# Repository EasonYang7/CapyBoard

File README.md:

# CapyBoard

Capyboard is a custom designed 80% TKL with custom knobs & OLED screen to fuel the exciting daily workload!

Inspired from the cute Capybara, the keyboard is a cozy comfort to all students studying for exams, and locking in for academics :)

## Features:
- Top & Bottom 3D Modelled Case
- 1x 128x64 OLED Display
- 2x Rotary Knob
- 79x RGB LEDs
- 79x Keys
- KMK Support

## BOM:
- 79x Cherry MX Switches
- 79x SK6812 Mini LEDs
- 79x 1N4148 Diodes
- 1x 128x64 OLED Screen
- 2x 4.7k 0603 Resistors
- 2x EC11E Rotary Encoders
- 1x Seeed Studio Xiao
- 1x Raspberry Pi Pico
- 1x Keycap Set

## Microcontroller
This keyboard supports two microcontroller options:
- Seeed Studio Xiao RP2040 (Main Usage)
- Raspberry Pi Pico (Alternative Usage if Needed)

Both firmware files will be used for seperate input purposes

## Flashing Firmware:

### Step 1 - Install MicroPython
1. Hold BOOTSEL Button on XIAO, and plug in USB-C
2. Download MicroPython .uf2 from https://micropython.org/download/SEEED_XIAO_RP2040/
3. Drag and Drop .uf2 file into RPI-RP2 Drive

### Step 2 - Install KMK
1. Download KMK from https://github.com/KMKfw/kmk_firmware
2. Copy the kmk folder to my XIAO

**Step 3 - Flash Keyboard Firmware**
1. Copy XIAO_code.py to your XIAO and rename it main.py

## Assembly
- Solder components using the schematic as reference
- Install switches onto PCB
- 3D Print the Case
- Use M2 Screws to Assemble the Chassis
- Flash Firmware onto the Keyboard!

## Usage
- Plug USB-C Cable to the Seeed Xiao Studio RP2040
- Keys are Mapped, and can be Modified using KMK!

## Pictures
Schematics:

PCB:

3D Model:

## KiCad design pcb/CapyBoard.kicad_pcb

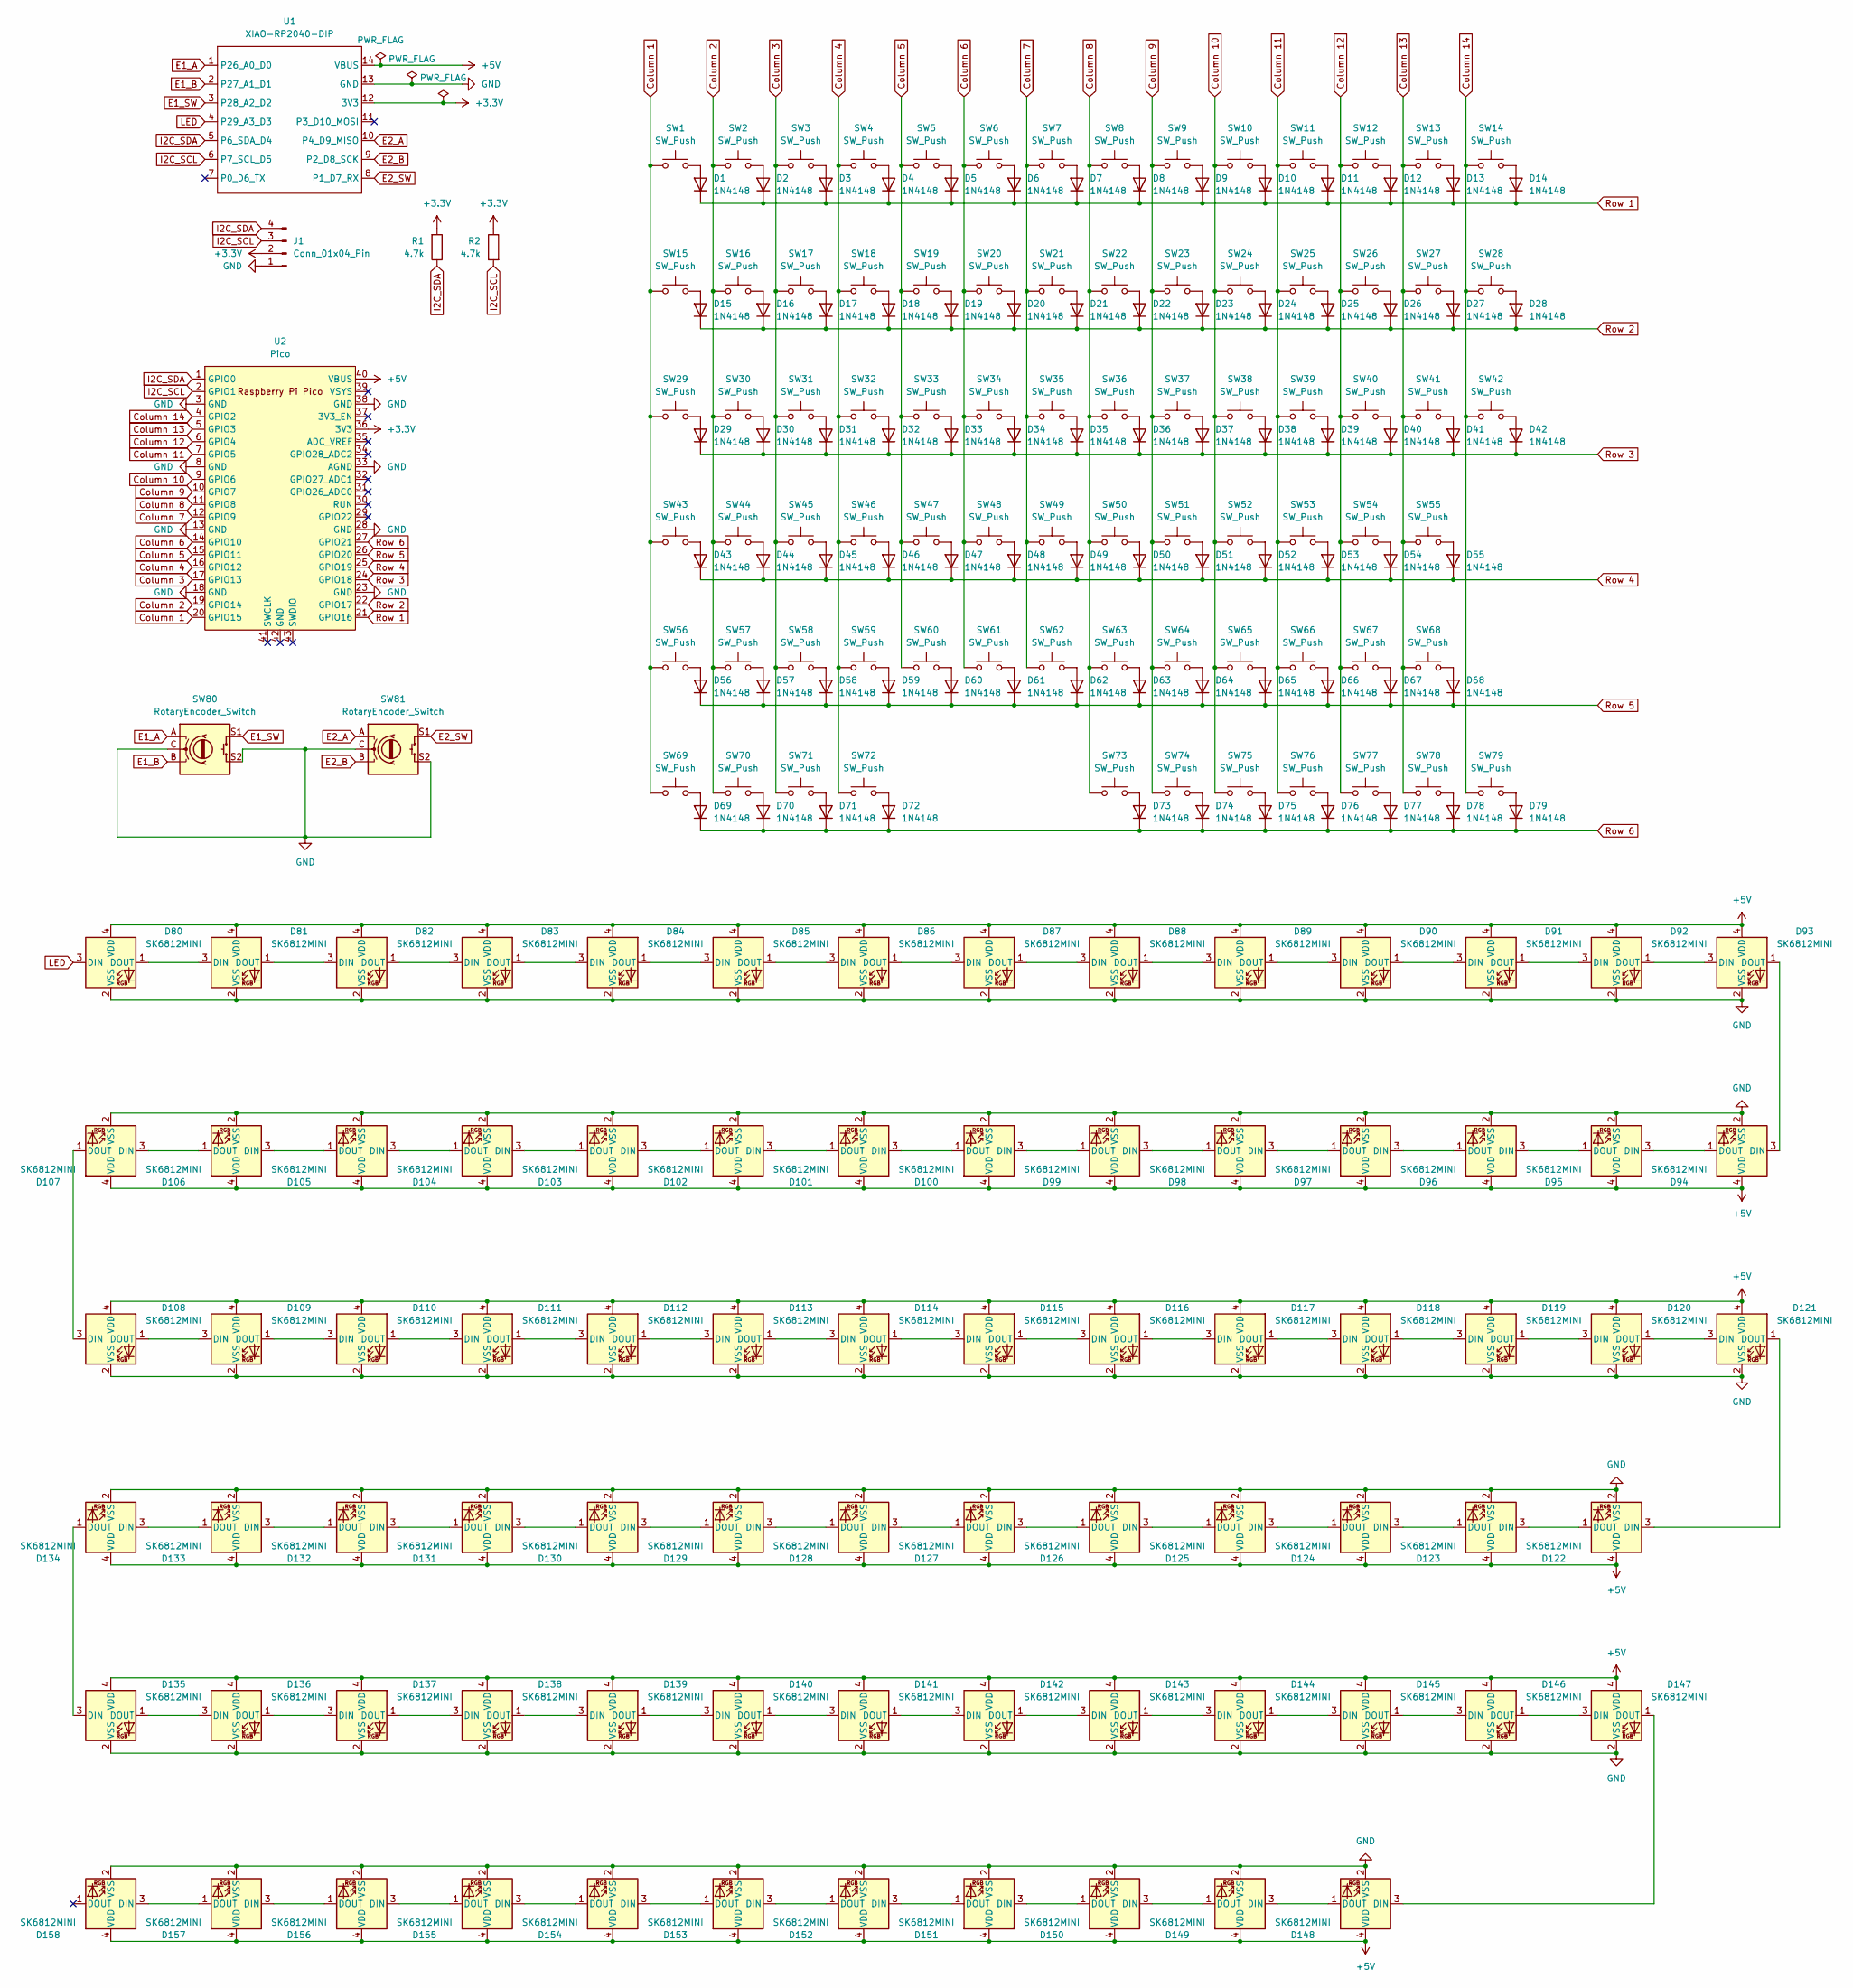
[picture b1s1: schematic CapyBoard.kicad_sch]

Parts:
D1, D2, D3, D4, D5, D6, D7, D8, D9, D10, D11, D12, D13, D14, D15, D16, D17, D18, D19, D20, D21, D22, D23, D24, D25, D26, D27, D28, D29, D30, D31, D32, D33, D34, D35, D36, D37, D38, D39, D40, D41, D42, D43, D44, D45, D46, D47, D48, D49, D50, D51, D52, D53, D54, D55, D56, D57, D58, D59, D60, D61, D62, D63, D64, D65, D66, D67, D68, D69, D70, D71, D72, D73, D74, D75, D76, D77, D78, D79: 1N4148; D_DO-35_SOD27_P7.62mm_Horizontal
D80, D81, D82, D83, D84, D85, D86, D87, D88, D89, D90, D91, D92, D93, D94, D95, D96, D97, D98, D99, D100, D101, D102, D103, D104, D105, D106, D107, D108, D109, D110, D111, D112, D113, D114, D115, D116, D117, D118, D119, D120, D121, D122, D123, D124, D125, D126, D127, D128, D129, D130, D131, D132, D133, D134, D135, D136, D137, D138, D139, D140, D141, D142, D143, D144, D145, D146, D147, D148, D149, D150, D151, D152, D153, D154, D155, D156, D157, D158: SK6812MINI; LED_SK6812MINI_PLCC4_3.5x3.5mm_P1.75mm
J1: Conn_01x04_Pin; 128x64OLED
R1, R2: 4.7k; R_0603_1608Metric_Pad0.98x0.95mm_HandSolder
SW1, SW2, SW3, SW4, SW5, SW6, SW7, SW8, SW9, SW10, SW11, SW12, SW13, SW14, SW15, SW16, SW17, SW18, SW19, SW20, SW21, SW22, SW23, SW24, SW25, SW26, SW27, SW30, SW31, SW32, SW33, SW34, SW35, SW36, SW37, SW38, SW39, SW40, SW41, SW44, SW45, SW46, SW47, SW48, SW49, SW50, SW51, SW52, SW53, SW54, SW57, SW58, SW59, SW60, SW61, SW62, SW63, SW64, SW65, SW66, SW68, SW77, SW78, SW79: SW_Push; SW_Cherry_MX_1.00u_PCB
SW28: SW_Push; SW_Cherry_MX_2.00u_PCB
SW29, SW42: SW_Push; SW_Cherry_MX_1.50u_PCB
SW43: SW_Push; SW_Cherry_MX_1.75u_PCB
SW55, SW56: SW_Push; SW_Cherry_MX_2.25u_PCB
SW67: SW_Push; SW_Cherry_MX_2.75u_PCB
SW69, SW70, SW71, SW73, SW74, SW75, SW76: SW_Push; SW_Cherry_MX_1.25u_PCB
SW72: SW_Push; SW_Cherry_MX_6.25u_PCB
SW80, SW81: RotaryEncoder_Switch; RotaryEncoder_Alps_EC11E-Switch_Vertical_H20mm_CircularMoun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
U1: XIAO-RP2040-DIP
U2: Pico; RPi_Pico_SMD_TH

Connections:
+3.3V: J1.2, R1.2, R2.1, U1.12 (3V3), U2.36 (3V3)
+5V: D80.4 (VDD), D81.4 (VDD), D82.4 (VDD), D83.4 (VDD), D84.4 (VDD), D85.4 (VDD), D86.4 (VDD), D87.4 (VDD), D88.4 (VDD), D89.4 (VDD), D90.4 (VDD), D91.4 (VDD), D92.4 (VDD), D93.4 (VDD), D94.4 (VDD), D95.4 (VDD), D96.4 (VDD), D97.4 (VDD), D98.4 (VDD), D99.4 (VDD), D100.4 (VDD), D101.4 (VDD), D102.4 (VDD), D103.4 (VDD), D104.4 (VDD), D105.4 (VDD), D106.4 (VDD), D107.4 (VDD), D108.4 (VDD), D109.4 (VDD), D110.4 (VDD), D111.4 (VDD), D112.4 (VDD), D113.4 (VDD), D114.4 (VDD), D115.4 (VDD), D116.4 (VDD), D117.4 (VDD), D118.4 (VDD), D119.4 (VDD), D120.4 (VDD), D121.4 (VDD), D122.4 (VDD), D123.4 (VDD), D124.4 (VDD), D125.4 (VDD), D126.4 (VDD), D127.4 (VDD), D128.4 (VDD), D129.4 (VDD), D130.4 (VDD), D131.4 (VDD), D132.4 (VDD), D133.4 (VDD), D134.4 (VDD), D135.4 (VDD), D136.4 (VDD), D137.4 (VDD), D138.4 (VDD), D139.4 (VDD), D140.4 (VDD), D141.4 (VDD), D142.4 (VDD), D143.4 (VDD), D144.4 (VDD), D145.4 (VDD), D146.4 (VDD), D147.4 (VDD), D148.4 (VDD), D149.4 (VDD), D150.4 (VDD), D151.4 (VDD), D152.4 (VDD), D153.4 (VDD), D154.4 (VDD), D155.4 (VDD), D156.4 (VDD), D157.4 (VDD), D158.4 (VDD), U1.14 (VBUS), U2.40 (VBUS)
Column 1: SW1.1, SW15.1, SW29.1, SW43.1, SW56.1, SW69.1, U2.20 (GPIO15)
Column 2: SW2.1, SW16.1, SW30.1, SW44.1, SW57.1, SW70.1, U2.19 (GPIO14)
Column 3: SW3.1, SW17.1, SW31.1, SW45.1, SW58.1, SW71.1, U2.17 (GPIO13)
Column 4: SW4.1, SW18.1, SW32.1, SW46.1, SW59.1, SW72.1, U2.16 (GPIO12)
Column 5: SW5.1, SW19.1, SW33.1, SW47.1, SW60.1, U2.15 (GPIO11)
Column 6: SW6.1, SW20.1, SW34.1, SW48.1, SW61.1, U2.14 (GPIO10)
Column 7: SW7.1, SW21.1, SW35.1, SW49.1, SW62.1, U2.12 (GPIO9)
Column 8: SW8.1, SW22.1, SW36.1, SW50.1, SW63.1, SW73.1, U2.11 (GPIO8)
Column 9: SW9.1, SW23.1, SW37.1, SW51.1, SW64.1, SW74.1, U2.10 (GPIO7)
Column 10: SW10.1, SW24.1, SW38.1, SW52.1, SW65.1, SW75.1, U2.9 (GPIO6)
Column 11: SW11.1, SW25.1, SW39.1, SW53.1, SW66.1, SW76.1, U2.7 (GPIO5)
Column 12: SW12.1, SW26.1, SW40.1, SW54.1, SW67.1, SW77.1, U2.6 (GPIO4)
Column 13: SW13.1, SW27.1, SW41.1, SW55.1, SW68.1, SW78.1, U2.5 (GPIO3)
Column 14: SW14.1, SW28.1, SW42.1, SW79.1, U2.4 (GPIO2)
E1_A: SW80.A, U1.1 (P26_A0_D0)
E1_B: SW80.B, U1.2 (P27_A1_D1)
E1_SW: SW80.S1, U1.3 (P28_A2_D2)
E2_A: SW81.A, U1.10 (P4_D9_MISO)
E2_B: SW81.B, U1.9 (P2_D8_SCK)
E2_SW: SW81.S1, U1.8 (P1_D7_RX)
GND: D80.2 (VSS), D81.2 (VSS), D82.2 (VSS), D83.2 (VSS), D84.2 (VSS), D85.2 (VSS), D86.2 (VSS), D87.2 (VSS), D88.2 (VSS), D89.2 (VSS), D90.2 (VSS), D91.2 (VSS), D92.2 (VSS), D93.2 (VSS), D94.2 (VSS), D95.2 (VSS), D96.2 (VSS), D97.2 (VSS), D98.2 (VSS), D99.2 (VSS), D100.2 (VSS), D101.2 (VSS), D102.2 (VSS), D103.2 (VSS), D104.2 (VSS), D105.2 (VSS), D106.2 (VSS), D107.2 (VSS), D108.2 (VSS), D109.2 (VSS), D110.2 (VSS), D111.2 (VSS), D112.2 (VSS), D113.2 (VSS), D114.2 (VSS), D115.2 (VSS), D116.2 (VSS), D117.2 (VSS), D118.2 (VSS), D119.2 (VSS), D120.2 (VSS), D121.2 (VSS), D122.2 (VSS), D123.2 (VSS), D124.2 (VSS), D125.2 (VSS), D126.2 (VSS), D127.2 (VSS), D128.2 (VSS), D129.2 (VSS), D130.2 (VSS), D131.2 (VSS), D132.2 (VSS), D133.2 (VSS), D134.2 (VSS), D135.2 (VSS), D136.2 (VSS), D137.2 (VSS), D138.2 (VSS), D139.2 (VSS), D140.2 (VSS), D141.2 (VSS), D142.2 (VSS), D143.2 (VSS), D144.2 (VSS), D145.2 (VSS), D146.2 (VSS), D147.2 (VSS), D148.2 (VSS), D149.2 (VSS), D150.2 (VSS), D151.2 (VSS), D152.2 (VSS), D153.2 (VSS), D154.2 (VSS), D155.2 (VSS), D156.2 (VSS), D157.2 (VSS), D158.2 (VSS), J1.1, SW80.C, SW80.MP, SW80.S2, SW81.C, SW81.MP, SW81.S2, U1.13 (GND), U2.3 (GND), U2.8 (GND), U2.13 (GND), U2.18 (GND), U2.23 (GND), U2.28 (GND), U2.33 (AGND), U2.38 (GND)
I2C_SCL: J1.3, R2.2, U1.6 (P7_SCL_D5), U2.2 (GPIO1)
I2C_SDA: J1.4, R1.1, U1.5 (P6_SDA_D4), U2.1 (GPIO0)
LED: D80.3 (DIN), U1.4 (P29_A3_D3)
unnamed: D1.2 (A), SW1.2
unnamed: D2.2 (A), SW2.2
unnamed: D3.2 (A), SW3.2
unnamed: D4.2 (A), SW4.2
unnamed: D5.2 (A), SW5.2
unnamed: D6.2 (A), SW6.2
unnamed: D7.2 (A), SW7.2
unnamed: D8.2 (A), SW8.2
unnamed: D9.2 (A), SW9.2
unnamed: D10.2 (A), SW10.2
unnamed: D11.2 (A), SW11.2
unnamed: D12.2 (A), SW12.2
unnamed: D13.2 (A), SW13.2
unnamed: D14.2 (A), SW14.2
unnamed: D15.2 (A), SW15.2
unnamed: D16.2 (A), SW16.2
unnamed: D17.2 (A), SW17.2
unnamed: D18.2 (A), SW18.2
unnamed: D19.2 (A), SW19.2
unnamed: D20.2 (A), SW20.2
unnamed: D21.2 (A), SW21.2
unnamed: D22.2 (A), SW22.2
unnamed: D23.2 (A), SW23.2
unnamed: D24.2 (A), SW24.2
unnamed: D25.2 (A), SW25.2
unnamed: D26.2 (A), SW26.2
unnamed: D27.2 (A), SW27.2
unnamed: D28.2 (A), SW28.2
unnamed: D29.2 (A), SW29.2
unnamed: D30.2 (A), SW30.2
unnamed: D31.2 (A), SW31.2
unnamed: D32.2 (A), SW32.2
unnamed: D33.2 (A), SW33.2
unnamed: D34.2 (A), SW34.2
unnamed: D35.2 (A), SW35.2
unnamed: D36.2 (A), SW36.2
unnamed: D37.2 (A), SW37.2
unnamed: D38.2 (A), SW38.2
unnamed: D39.2 (A), SW39.2
unnamed: D40.2 (A), SW40.2
unnamed: D41.2 (A), SW41.2
unnamed: D42.2 (A), SW42.2
unnamed: D43.2 (A), SW43.2
unnamed: D44.2 (A), SW44.2
unnamed: D45.2 (A), SW45.2
unnamed: D46.2 (A), SW46.2
unnamed: D47.2 (A), SW47.2
unnamed: D48.2 (A), SW48.2
unnamed: D49.2 (A), SW49.2
unnamed: D50.2 (A), SW50.2
unnamed: D51.2 (A), SW51.2
unnamed: D52.2 (A), SW52.2
unnamed: D53.2 (A), SW53.2
unnamed: D54.2 (A), SW54.2
unnamed: D55.2 (A), SW55.2
unnamed: D56.2 (A), SW56.2
unnamed: D57.2 (A), SW57.2
unnamed: D58.2 (A), SW58.2
unnamed: D59.2 (A), SW59.2
unnamed: D60.2 (A), SW60.2
unnamed: D61.2 (A), SW61.2
unnamed: D62.2 (A), SW62.2
unnamed: D63.2 (A), SW63.2
unnamed: D64.2 (A), SW64.2
unnamed: D65.2 (A), SW65.2
unnamed: D66.2 (A), SW66.2
unnamed: D67.2 (A), SW67.2
unnamed: D68.2 (A), SW68.2
unnamed: D69.2 (A), SW69.2
unnamed: D70.2 (A), SW70.2
unnamed: D71.2 (A), SW71.2
unnamed: D72.2 (A), SW72.2
unnamed: D73.2 (A), SW73.2
unnamed: D74.2 (A), SW74.2
unnamed: D75.2 (A), SW75.2
unnamed: D76.2 (A), SW76.2
unnamed: D77.2 (A), SW77.2
unnamed: D78.2 (A), SW78.2
unnamed: D79.2 (A), SW79.2
unnamed: D80.1 (DOUT), D81.3 (DIN)
unnamed: D81.1 (DOUT), D82.3 (DIN)
unnamed: D82.1 (DOUT), D83.3 (DIN)
unnamed: D83.1 (DOUT), D84.3 (DIN)
unnamed: D84.1 (DOUT), D85.3 (DIN)
unnamed: D85.1 (DOUT), D86.3 (DIN)
unnamed: D86.1 (DOUT), D87.3 (DIN)
unnamed: D87.1 (DOUT), D88.3 (DIN)
unnamed: D88.1 (DOUT), D89.3 (DIN)
unnamed: D89.1 (DOUT), D90.3 (DIN)
unnamed: D90.1 (DOUT), D91.3 (DIN)
unnamed: D91.1 (DOUT), D92.3 (DIN)
unnamed: D92.1 (DOUT), D93.3 (DIN)
unnamed: D93.1 (DOUT), D94.3 (DIN)
unnamed: D94.1 (DOUT), D95.3 (DIN)
unnamed: D95.1 (DOUT), D96.3 (DIN)
unnamed: D96.1 (DOUT), D97.3 (DIN)
unnamed: D97.1 (DOUT), D98.3 (DIN)
unnamed: D98.1 (DOUT), D99.3 (DIN)
unnamed: D99.1 (DOUT), D100.3 (DIN)
unnamed: D100.1 (DOUT), D101.3 (DIN)
unnamed: D101.1 (DOUT), D102.3 (DIN)
unnamed: D102.1 (DOUT), D103.3 (DIN)
unnamed: D103.1 (DOUT), D104.3 (DIN)
unnamed: D104.1 (DOUT), D105.3 (DIN)
unnamed: D105.1 (DOUT), D106.3 (DIN)
unnamed: D106.1 (DOUT), D107.3 (DIN)
unnamed: D107.1 (DOUT), D108.3 (DIN)
unnamed: D108.1 (DOUT), D109.3 (DIN)
unnamed: D109.1 (DOUT), D110.3 (DIN)
unnamed: D110.1 (DOUT), D111.3 (DIN)
unnamed: D111.1 (DOUT), D112.3 (DIN)
unnamed: D112.1 (DOUT), D113.3 (DIN)
unnamed: D113.1 (DOUT), D114.3 (DIN)
unnamed: D114.1 (DOUT), D115.3 (DIN)
unnamed: D115.1 (DOUT), D116.3 (DIN)
unnamed: D116.1 (DOUT), D117.3 (DIN)
unnamed: D117.1 (DOUT), D118.3 (DIN)
unnamed: D118.1 (DOUT), D119.3 (DIN)
unnamed: D119.1 (DOUT), D120.3 (DIN)
unnamed: D120.1 (DOUT), D121.3 (DIN)
unnamed: D121.1 (DOUT), D122.3 (DIN)
unnamed: D122.1 (DOUT), D123.3 (DIN)
unnamed: D123.1 (DOUT), D124.3 (DIN)
unnamed: D124.1 (DOUT), D125.3 (DIN)
unnamed: D125.1 (DOUT), D126.3 (DIN)
unnamed: D126.1 (DOUT), D127.3 (DIN)
unnamed: D127.1 (DOUT), D128.3 (DIN)
unnamed: D128.1 (DOUT), D129.3 (DIN)
unnamed: D129.1 (DOUT), D130.3 (DIN)
unnamed: D130.1 (DOUT), D131.3 (DIN)
unnamed: D131.1 (DOUT), D132.3 (DIN)
unnamed: D132.1 (DOUT), D133.3 (DIN)
unnamed: D133.1 (DOUT), D134.3 (DIN)
unnamed: D134.1 (DOUT), D135.3 (DIN)
unnamed: D135.1 (DOUT), D136.3 (DIN)
unnamed: D136.1 (DOUT), D137.3 (DIN)
unnamed: D137.1 (DOUT), D138.3 (DIN)
unnamed: D138.1 (DOUT), D139.3 (DIN)
unnamed: D139.1 (DOUT), D140.3 (DIN)
unnamed: D140.1 (DOUT), D141.3 (DIN)
unnamed: D141.1 (DOUT), D142.3 (DIN)
unnamed: D142.1 (DOUT), D143.3 (DIN)
unnamed: D143.1 (DOUT), D144.3 (DIN)
unnamed: D144.1 (DOUT), D145.3 (DIN)
unnamed: D145.1 (DOUT), D146.3 (DIN)
unnamed: D146.1 (DOUT), D147.3 (DIN)
unnamed: D147.1 (DOUT), D148.3 (DIN)
unnamed: D148.1 (DOUT), D149.3 (DIN)
unnamed: D149.1 (DOUT), D150.3 (DIN)
unnamed: D150.1 (DOUT), D151.3 (DIN)
unnamed: D151.1 (DOUT), D152.3 (DIN)
unnamed: D152.1 (DOUT), D153.3 (DIN)
unnamed: D153.1 (DOUT), D154.3 (DIN)
unnamed: D154.1 (DOUT), D155.3 (DIN)
unnamed: D155.1 (DOUT), D156.3 (DIN)
unnamed: D156.1 (DOUT), D157.3 (DIN)
unnamed: D157.1 (DOUT), D158.3 (DIN)
Row 1: D1.1 (K), D2.1 (K), D3.1 (K), D4.1 (K), D5.1 (K), D6.1 (K), D7.1 (K), D8.1 (K), D9.1 (K), D10.1 (K), D11.1 (K), D12.1 (K), D13.1 (K), D14.1 (K), U2.21 (GPIO16)
Row 2: D15.1 (K), D16.1 (K), D17.1 (K), D18.1 (K), D19.1 (K), D20.1 (K), D21.1 (K), D22.1 (K), D23.1 (K), D24.1 (K), D25.1 (K), D26.1 (K), D27.1 (K), D28.1 (K), U2.22 (GPIO17)
Row 3: D29.1 (K), D30.1 (K), D31.1 (K), D32.1 (K), D33.1 (K), D34.1 (K), D35.1 (K), D36.1 (K), D37.1 (K), D38.1 (K), D39.1 (K), D40.1 (K), D41.1 (K), D42.1 (K), U2.24 (GPIO18)
Row 4: D43.1 (K), D44.1 (K), D45.1 (K), D46.1 (K), D47.1 (K), D48.1 (K), D49.1 (K), D50.1 (K), D51.1 (K), D52.1 (K), D53.1 (K), D54.1 (K), D55.1 (K), U2.25 (GPIO19)
Row 5: D56.1 (K), D57.1 (K), D58.1 (K), D59.1 (K), D60.1 (K), D61.1 (K), D62.1 (K), D63.1 (K), D64.1 (K), D65.1 (K), D66.1 (K), D67.1 (K), D68.1 (K), U2.26 (GPIO20)
Row 6: D69.1 (K), D70.1 (K), D71.1 (K), D72.1 (K), D73.1 (K), D74.1 (K), D75.1 (K), D76.1 (K), D77.1 (K), D78.1 (K), D79.1 (K), U2.27 (GPIO21)

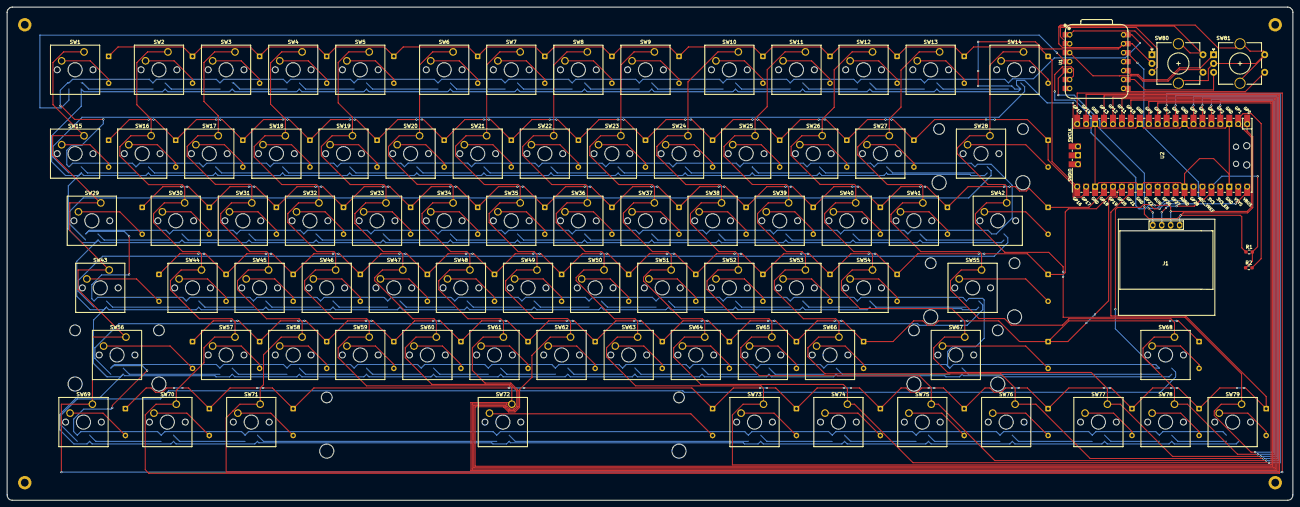
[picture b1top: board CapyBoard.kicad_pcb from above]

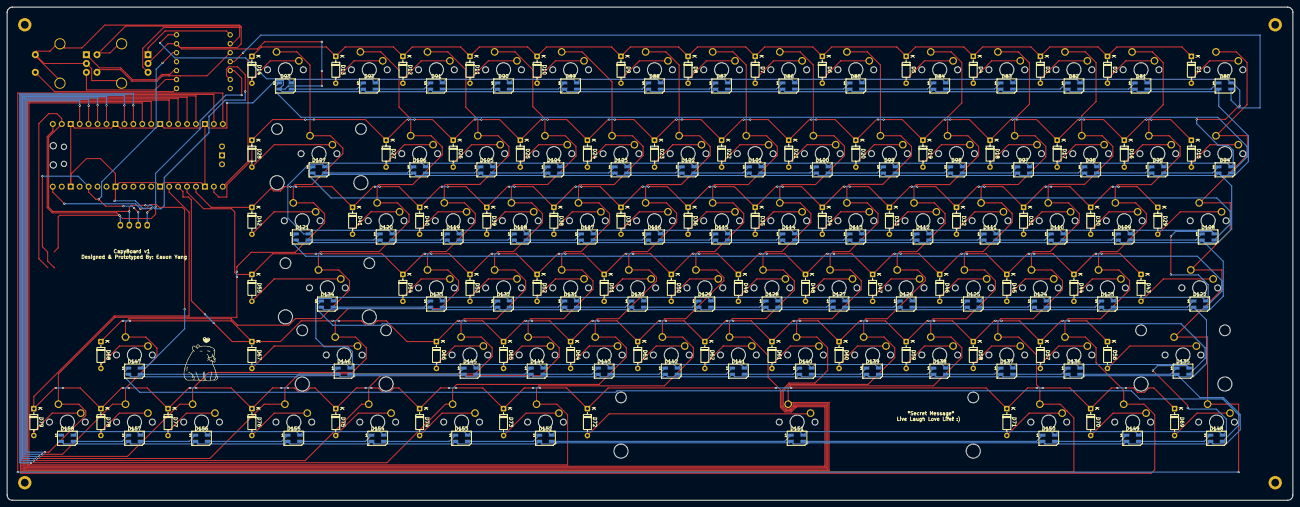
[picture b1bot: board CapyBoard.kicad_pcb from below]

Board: 2 copper layers, 365.0 x 140.0 mm, 244 parts (158 on the bottom side), 189 nets.

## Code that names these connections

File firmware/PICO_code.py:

# CapyBoard — Pico Firmware (code.py)

import board
from kmk.kmk_keyboard import KMKKeyboard
from kmk.keys import KC
from kmk.scanners import DiodeOrientation
from kmk.modules.layers import Layers
from kmk.modules.split import Split, SplitType, SplitSide
from kmk.extensions.media_keys import MediaKeys

keyboard = KMKKeyboard()

# Split configuration
split = Split(
    split_type=SplitType.I2C,
    split_side=SplitSide.RIGHT,
    data_pin=board.GP0,  
    data_pin2=board.GP1,   
)

# Column pins (GPIO2-GPIO15)
keyboard.col_pins = (
    board.GP15,
    board.GP14, 
    board.GP13,  
    board.GP12, 
    board.GP11,  
    board.GP10, 
    board.GP9,  
    board.GP8,  
    board.GP7,
    board.GP6,  
    board.GP5, 
    board.GP4,  
    board.GP3,  
    board.GP2,  
)

# ─── Row pins (GPIO16-GPIO21)
keyboard.row_pins = (
    board.GP16, 
    board.GP17,  
    board.GP18, 
    board.GP19, 
    board.GP20, 
    board.GP21,  
)

keyboard.diode_orientation = DiodeOrientation.COL2ROW

# Modules
layers = Layers()
media_keys = MediaKeys()
keyboard.modules = [split, layers, media_keys]

# Keymap
_______ = KC.TRNS
XXXXXXX = KC.NO

keyboard.keymap = [
    # Layer 0 Base QWERTY
    [
        KC.ESC,   KC.N1,   KC.N2,   KC.N3,   KC.N4,   KC.N5,   KC.N6,   KC.N7,   KC.N8,   KC.N9,   KC.N0,   KC.MINS, KC.EQL,  KC.BSPC,
        KC.TAB,   KC.Q,    KC.W,    KC.E,    KC.R,    KC.T,    KC.Y,    KC.U,    KC.I,    KC.O,    KC.P,    KC.LBRC, KC.RBRC, KC.BSLS,
        KC.CAPS,  KC.A,    KC.S,    KC.D,    KC.F,    KC.G,    KC.H,    KC.J,    KC.K,    KC.L,    KC.SCLN, KC.QUOT, XXXXXXX, KC.ENT,
        KC.LSFT,  KC.Z,    KC.X,    KC.C,    KC.V,    KC.B,    KC.N,    KC.M,    KC.COMM, KC.DOT,  KC.SLSH, XXXXXXX, XXXXXXX, KC.RSFT,
        KC.LCTL,  KC.LGUI, KC.LALT, XXXXXXX, XXXXXXX, XXXXXXX, KC.SPC,  XXXXXXX, XXXXXXX, XXXXXXX, KC.RALT, KC.APP,  XXXXXXX, KC.RCTL,
        KC.MO(1), KC.F1,   KC.F2,   KC.F3,   XXXXXXX, KC.F4,   KC.F5,   KC.F6,   KC.F7,   KC.F8,   KC.F9,   KC.F10,  KC.F11,  KC.F12,
    ],
    # Layer 1 Function
    [
        KC.GRV,   KC.F1,   KC.F2,   KC.F3,   KC.F4,   KC.F5,   KC.F6,   KC.F7,   KC.F8,   KC.F9,   KC.F10,  KC.F11,  KC.F12,  KC.DEL,
        _______,  _______, KC.UP,   _______, _______, _______, _______, _______, _______, _______, _______, _______, _______, _______,
        _______,  KC.LEFT, KC.DOWN, KC.RGHT, _______, _______, _______, _______, _______, _______, _______, _______, _______, _______,
        _______,  _______, _______, _______, _______, _______, _______, _______, _______, _______, _______, _______, _______, _______,
        _______,  _______, _______, _______, _______, _______, _______, _______, _______, _______, _______, _______, _______, _______,
        _______,  _______, _______, _______, _______, _______, _______, _______, _______, _______, _______, _______, _______, _______,
    ],
    # Layer 2 Media
    [
        _______, KC.MUTE, KC.VOLD, KC.VOLU, KC.MPRV, KC.MPLY, KC.MNXT, _______, _______, _______, _______, _______, _______, _______,
        _______, _______, _______, _______, _______, _______, _______, _______, _______, _______, _______, _______, _______, _______,
        _______, _______, _______, _______, _______, _______, _______, _______, _______, _______, _______, _______, _______, _______,
        _______, _______, _______, _______, _______, _______, _______, _______, _______, _______, _______, _______, _______, _______,
        _______, _______, _______, _______, _______, _______, _______, _______, _______, _______, _______, _______, _______, _______,
        _______, _______, _______, _______, _______, _______, _______, _______, _______, _______, _______, _______, _______, _______,
    ],
]

if __name__ == '__main__':
    keyboard.go()

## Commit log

2026-03-22 Enhance README with inspiration description
    Add a brief description of the keyboard's inspiration.
2026-03-22 Correct diode model from IN4148 to 1N4148
2026-03-22 fixed gerber files
2026-03-22 modified the README, added new CAD files
2026-03-22 fix OLED quoting error in BOM.csv
2026-03-22 gerbers modification
2026-03-22 modified the README, and changed gerbers!
2026-03-22 Changed README files
2026-03-22 modified gerbers
2026-03-22 Update price and link for Seeed Xiao Studio RP2040
    Updated the price of Seeed Xiao Studio RP2040 and modified its link.
2026-03-22 Update Switch price and link in BOM.csv
    Updated the price and link for the MX Keyboard Switch.
2026-03-22 Update switch quantity and add new components
2026-03-22 Update OLED entry with current price and link
    Updated OLED price and link in BOM.
2026-03-22 Fix Resistors entry format in BOM.csv
    Updated the Resistors entry to clarify quantity and price format.
2026-03-22 Update prices for components in BOM.csv
    Updated the current prices and original prices for the Switch, LEDs, and OLED components in the BOM.
2026-03-22 Update component prices and links in BOM.csv
    Updated prices and links for components in BOM.
2026-03-22 Update OLED entry with new price and link
    Updated OLED price and link in BOM.
